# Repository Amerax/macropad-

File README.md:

# EZpad

A compact productivity macropad built around the Seeed Studio XIAO RP2040. The project includes a custom PCB designed in KiCad and QMK firmware, with 6 keys and a rotary encoder for everyday shortcuts like copy, paste, plus volume control and an OLED status display.

**Features:**
5 push-button keys + 1 rotary encoder with integrated push switch (6 keys total), wired direct-pin (no matrix). Not having matrix makes it much simpler and easy. 
Rotary encoder controls system volume 
0.91" I2C OLED display (SSD1306-compatible) for status.
Firmware built on QMK, running on a Seeed Studio XIAO RP2040.
Firmware is custom made persoanlly built. 

---
**Schematic**
The KiCad schematic shows the XIAO RP2040 connected directly to five push buttons and a rotary encoder using GPIO pins, plus an I2C-connected OLED display.
I made this all myself for the first time ever,
My very own first schema 

**PCB**
Same to be said about the pcb. It is quite simple enough, not as many traces as a motherboard haha. 

**Cad**
I used a bit of both onshape and fusion360. But here is image from onsahpe. 

**BOM**
Part	Quantity
Seeed Studio XIAO RP2040	1
Push-button switches	5
EC11 rotary encoder (w/ push switch)	1
0.91" I2C OLED display (SSD1306-compatible)	1
Custom PCB	1
USB-C cable	1

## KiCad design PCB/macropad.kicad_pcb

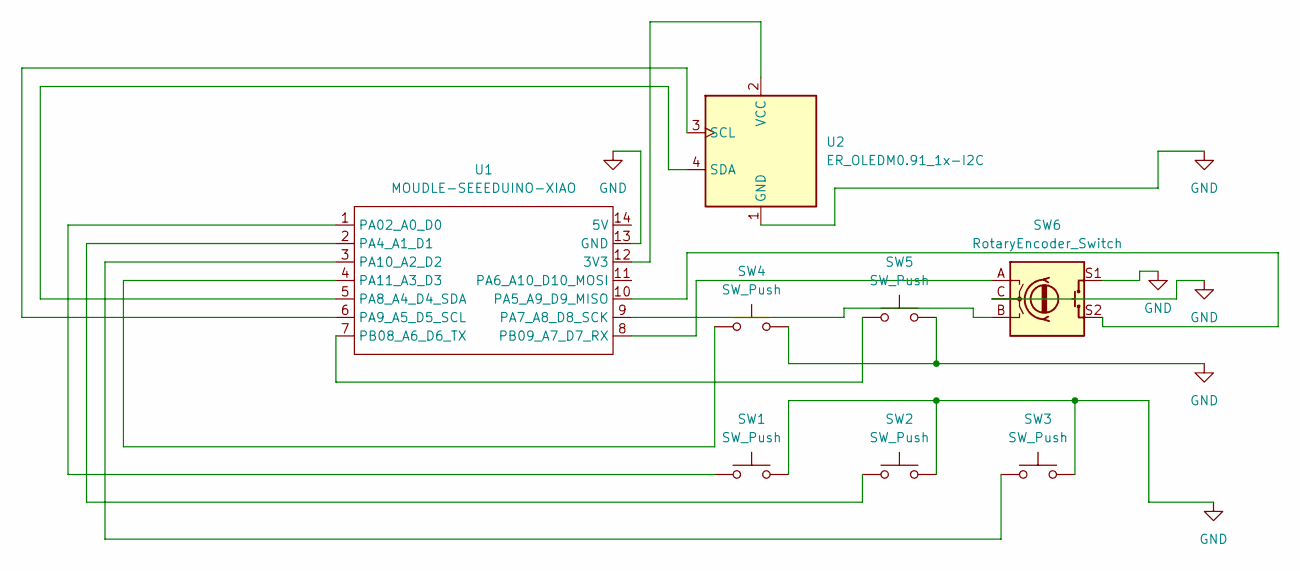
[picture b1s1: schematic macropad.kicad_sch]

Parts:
SW1, SW2, SW3, SW4, SW5: SW_Push; SW_Cherry_MX_1.00u_PCB
SW6: RotaryEncoder_Switch; RotaryEncoder_Alps_EC11E-Switch_Vertical_H20mm
U1: MOUDLE-SEEEDUINO-XIAO; XIAO-Generic-Hybrid-14P-2.54-21X17.8MM
U2: ER_OLEDM0.91_1x-I2C

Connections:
GND: SW1.2, SW2.2, SW3.2, SW4.2, SW5.2, SW6.C, SW6.S1, U1.13 (GND), U2.1 (GND)
unnamed: U1.12 (3V3), U2.2 (VCC)
unnamed: SW1.1, U1.1 (PA02_A0_D0)
unnamed: SW2.1, U1.2 (PA4_A1_D1)
unnamed: SW6.S2, U1.10 (PA5_A9_D9_MISO)
unnamed: SW6.B, U1.9 (PA7_A8_D8_SCK)
unnamed: U1.5 (PA8_A4_D4_SDA), U2.4 (SDA)
unnamed: U1.6 (PA9_A5_D5_SCL), U2.3 (SCL)
unnamed: SW3.1, U1.3 (PA10_A2_D2)
unnamed: SW4.1, U1.4 (PA11_A3_D3)
unnamed: SW5.1, U1.7 (PB08_A6_D6_TX)
unnamed: SW6.A, U1.8 (PB09_A7_D7_RX)

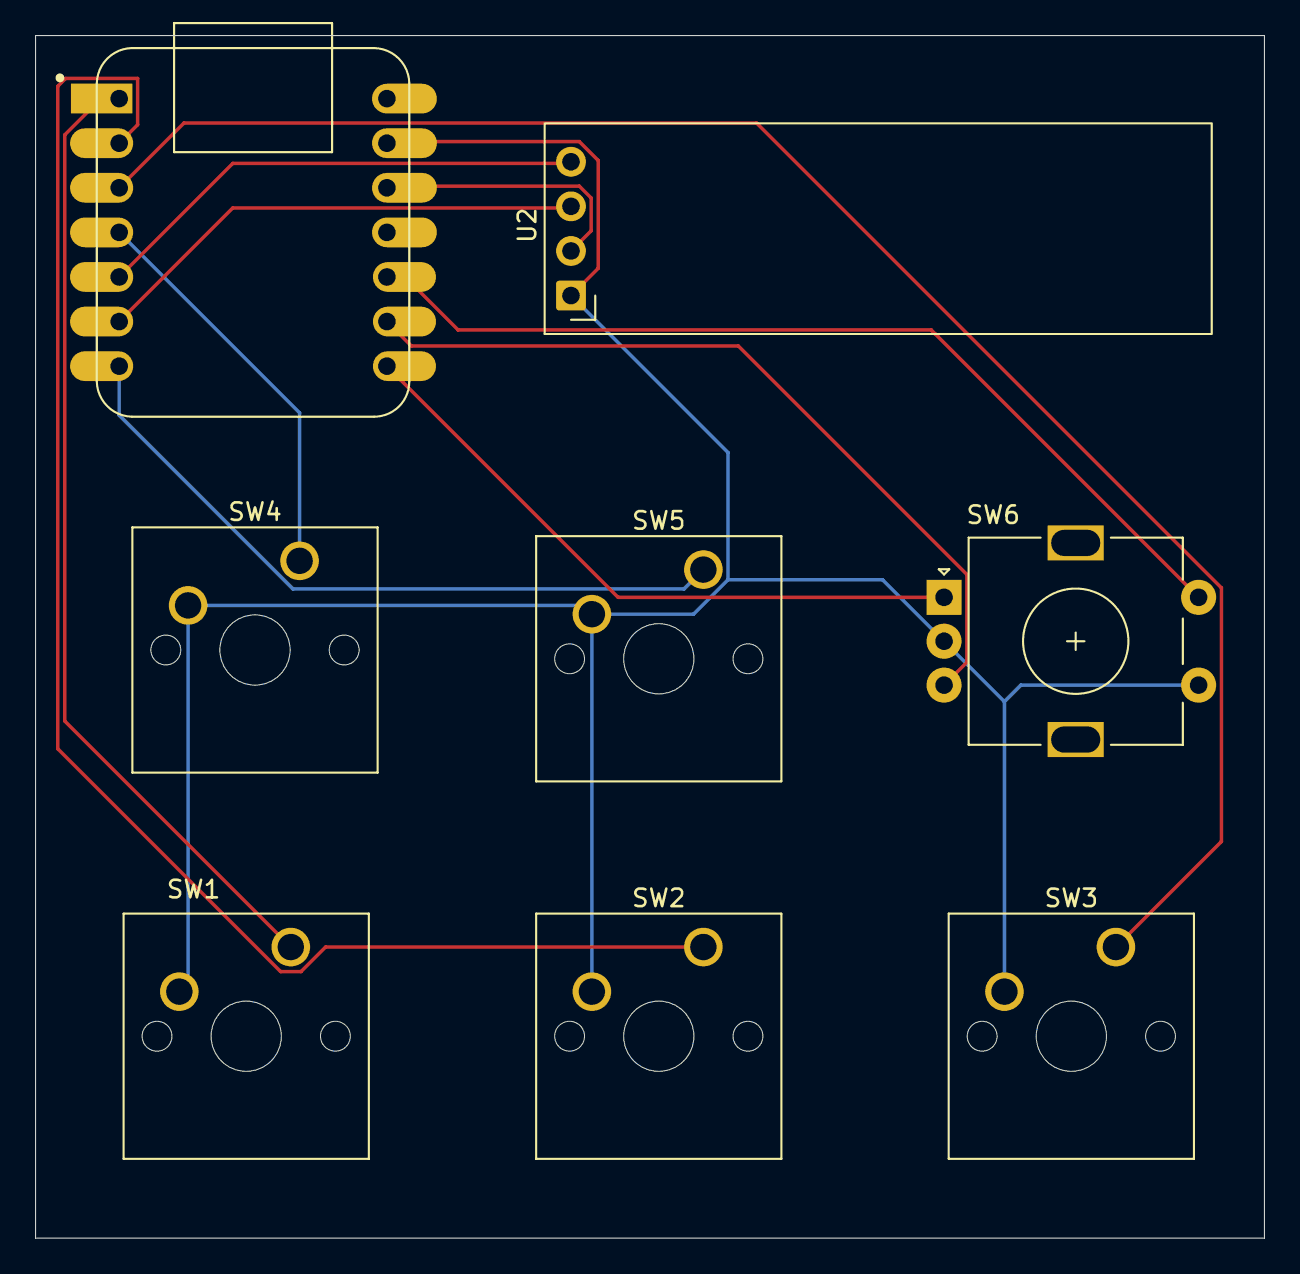
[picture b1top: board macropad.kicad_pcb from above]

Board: 2 copper layers, 70.0 x 68.5 mm, 8 parts (0 on the bottom side), 12 nets.
